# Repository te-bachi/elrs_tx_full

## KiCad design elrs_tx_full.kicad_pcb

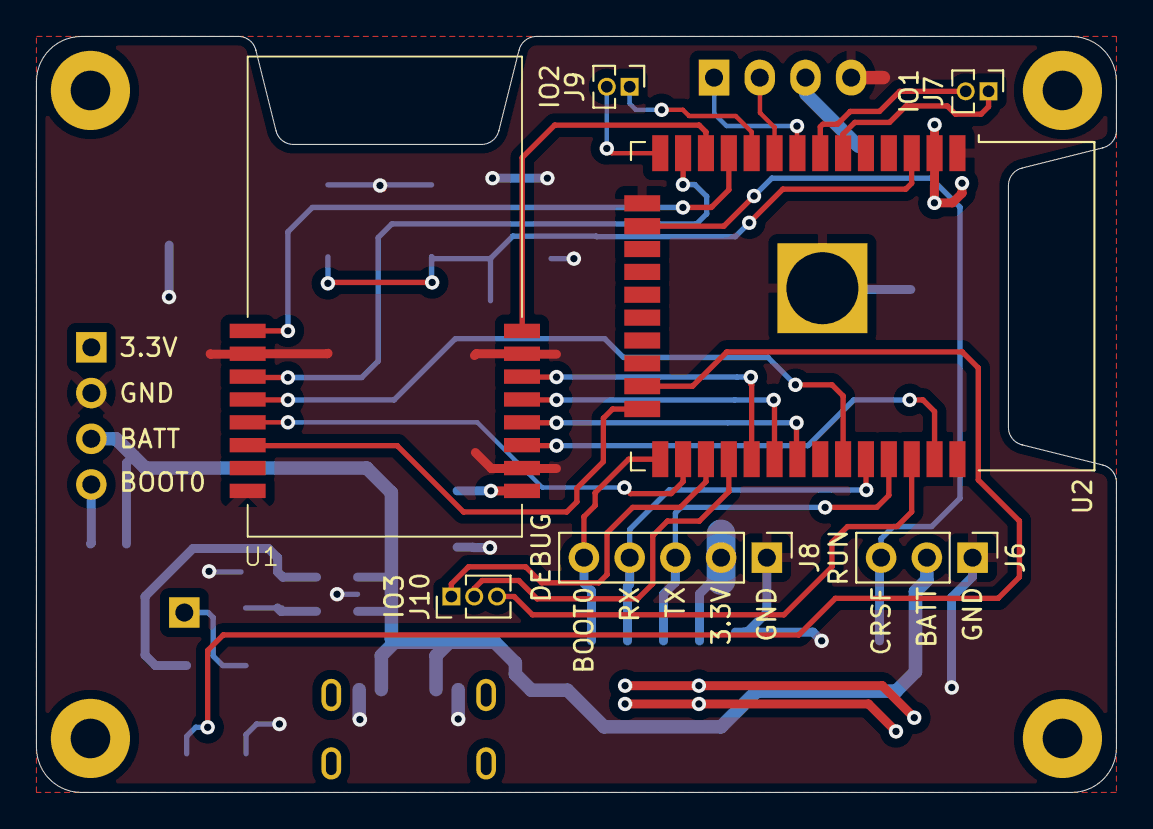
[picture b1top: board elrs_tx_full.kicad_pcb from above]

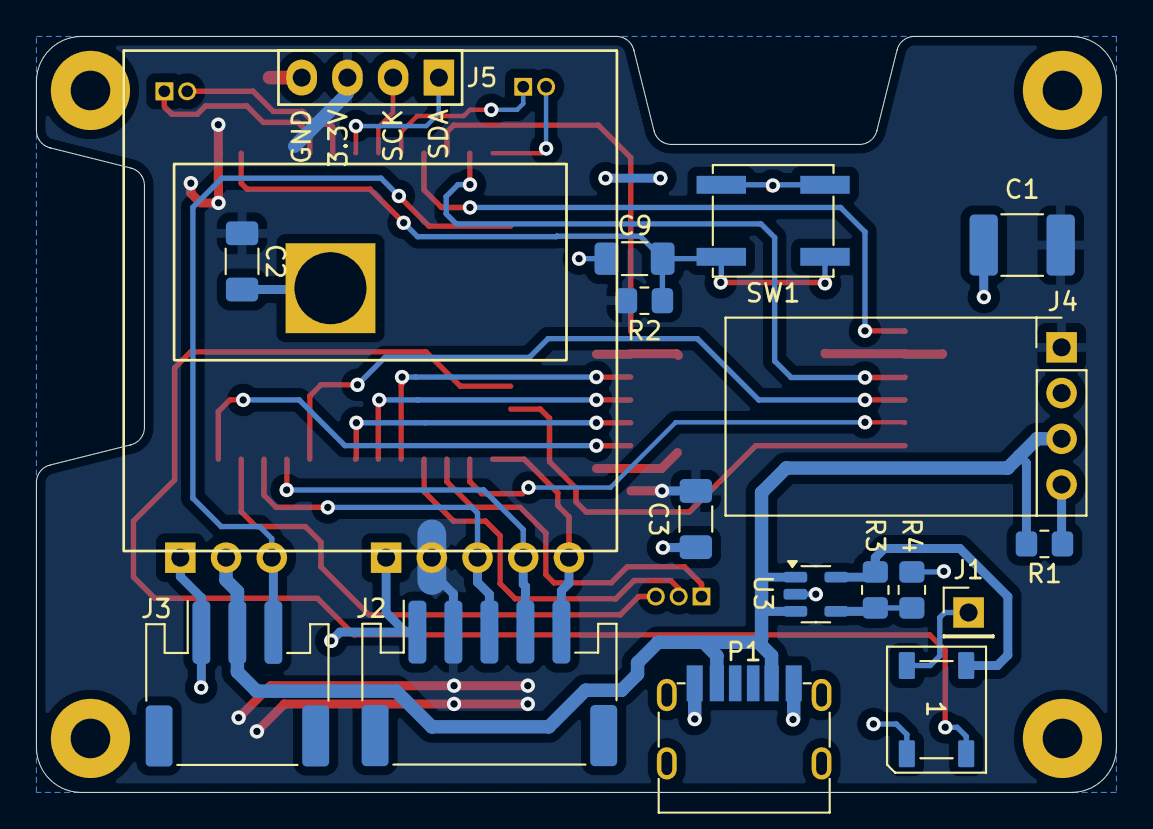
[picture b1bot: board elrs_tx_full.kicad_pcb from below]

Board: 2 copper layers, 60.0 x 42.0 mm, 28 parts (17 on the bottom side), 32 nets.

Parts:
C1: 10uF; C_1812_4532Metric_Pad1.57x3.40mm_HandSolder
C2, C3, C9: 10uF; C_1206_3216Metric_Pad1.33x1.80mm_HandSolder
D1: WS2812B; LED_WS2812B_PLCC4_5.0x5.0mm_P3.2mm
H1, H2, H3, H4: MountingHole; MountingHole_2.2mm_M2_Pad
J1: LED Chain; PinHeader_1x01_P2.54mm_Vertical
J2: DEBUG; JST_PH_S5B-PH-SM4-TB_1x05-1MP_P2.00mm_Horizontal
J3: RUN; JST_PH_S3B-PH-SM4-TB_1x03-1MP_P2.00mm_Horizontal
J4: DC_DC; DC_DC_20x11
J5: OLED_I2C; OLED_27.3x27.8mm_no_holes
J6: RUN; PinHeader_1x03_P2.54mm_Vertical
J7: IO1; PinHeader_1x02_P1.27mm_Vertical
J8: DEBUG; PinHeader_1x05_P2.54mm_Vertical
J9: IO2; PinHeader_1x02_P1.27mm_Vertical
J10: IO3; PinHeader_1x03_P1.27mm_Vertical
P1: USB_C_Plug_USB2.0; USB_C_DEALON_009
R1, R2: 10k; R_0805_2012Metric_Pad1.20x1.40mm_HandSolder
R3: 56k; R_0805_2012Metric_Pad1.20x1.40mm_HandSolder
R4: 22k; R_0805_2012Metric_Pad1.20x1.40mm_HandSolder
SW1: RESET; SW_SPST_EVQP0
U1: E28-2G4M27S-MY; E28-2G4M27S
U2: ESP32-WROOM-32-MY; ESP32-WROOM-32_zhaw
U3: SPX3819M5-L; SOT-23-5

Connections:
+3.3V: C1.1, C2.1, C3.1, J2.2, J4.1, J5.2, J8.2, R2.2, U1.1 (VCC), U2.2 (VDD)
+5V: D1.1 (VDD), R3.1, U3.5 (OUT)
+BATT: J3.2, J4.3, J6.2, P1.A9 (VBUS), P1.B9 (VBUS), R1.2, U3.1 (IN), U3.3 (EN)
/CRSF_RX_TX: J3.3, J6.3, U2.16 (IO13)
/E28_BUSY: U1.12 (BUSY), U2.33 (IO21)
/E28_DIO1: U1.13 (DIO1), U2.26 (IO4)
/E28_DIO2: U1.14 (DIO2), U2.24 (IO2)
/E28_MISO_RX: U1.4 (MOSI_RX), U2.31 (IO19)
/E28_MISO_TX: U1.3 (MISO_TX), U2.37 (IO23)
/E28_NRESET: U1.11 (NRESET), U2.13 (IO14)
/E28_NSS_CTS: U1.6 (NSS_CTS), U2.29 (IO5)
/E28_RX_EN: U1.8 (RX_EN), U2.12 (IO27)
/E28_SCK_RTS: U1.5 (SCK_RTS), U2.30 (IO18)
/E28_TX_EN: U1.9 (TX_EN), U2.11 (IO26)
/EN: C9.1, R2.1, SW1.2, U2.3 (EN)
/ESP32_BOOT0: J2.5, J8.5, U2.25 (IO0)
/ESP32_RX: J2.4, J8.4, U2.34 (RXD0/IO3)
/ESP32_TX: J2.3, J8.3, U2.35 (TXD0/IO1)
/IO12: J9.2, U2.14 (IO12)
/IO16: J10.1, U2.27 (IO16)
/IO17: J10.2, U2.28 (IO17)
/IO22: J10.3, U2.36 (IO22)
/IO25: J9.1, U2.10 (IO25)
/IO34: J7.1, U2.6 (IO34)
/IO35: J7.2, U2.7 (IO35)
/LED_RGB: D1.4 (DIN), U2.23 (IO15)
/OLED_SCK: J5.3, U2.9 (IO33)
/OLED_SDA: J5.4, U2.8 (IO32)
GND: C1.2, C2.2, C3.2, C9.2, D1.3 (VSS), J2.1, J3.1, J4.2, J5.1, J6.1, J8.1, P1.A12 (GND), P1.B12 (GND), R4.2, SW1.1, U1.2 (GND), U1.7 (GND), U1.10 (GND), U1.16 (GND), U2.1 (GND), U2.15 (GND), U2.38 (GND), U2.39 (GND), U3.2 (GND)
unnamed: D1.2 (DOUT), J1.1
unnamed: J4.4, R1.1
unnamed: R3.2, R4.1, U3.4 (ADJ)

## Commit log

2025-05-04 inital commit
2025-06-09 pcb progress
2025-06-17 remove unused
2025-06-17 add gerber
